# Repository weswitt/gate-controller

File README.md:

This project is a PCB design for controlling a Liftmaster gate operator from Home Assistant. 

The PCB design was done in KiCad 8.0, which is an open source electronic design tool. This project includes all of the KiCad project files so that you can modify the PCB if needed. I've also included a GERBER.ZIP file that can be used to simply have the PCB printed by someplace like JLPCB.

This project includes a bill of materials with URLs for all the parts necessary to build the board. I've sourced the part from DigiKey and Amazon.

The integration of the gate controller into Home Assistant is accomplished using ESPHome. This project includes the YAML file necessary to build and flash the firmware into the gate controller. You'll need to edit the YAML file and change the lines specified to customize to your environment.

This project includes datasheets for every component used on the gate controller board.

The gate controller board uses an ESP32-WROOM-32U microcontroller. This variant of the ESP32 uses an external antenna to improve the Wifi connectivity.

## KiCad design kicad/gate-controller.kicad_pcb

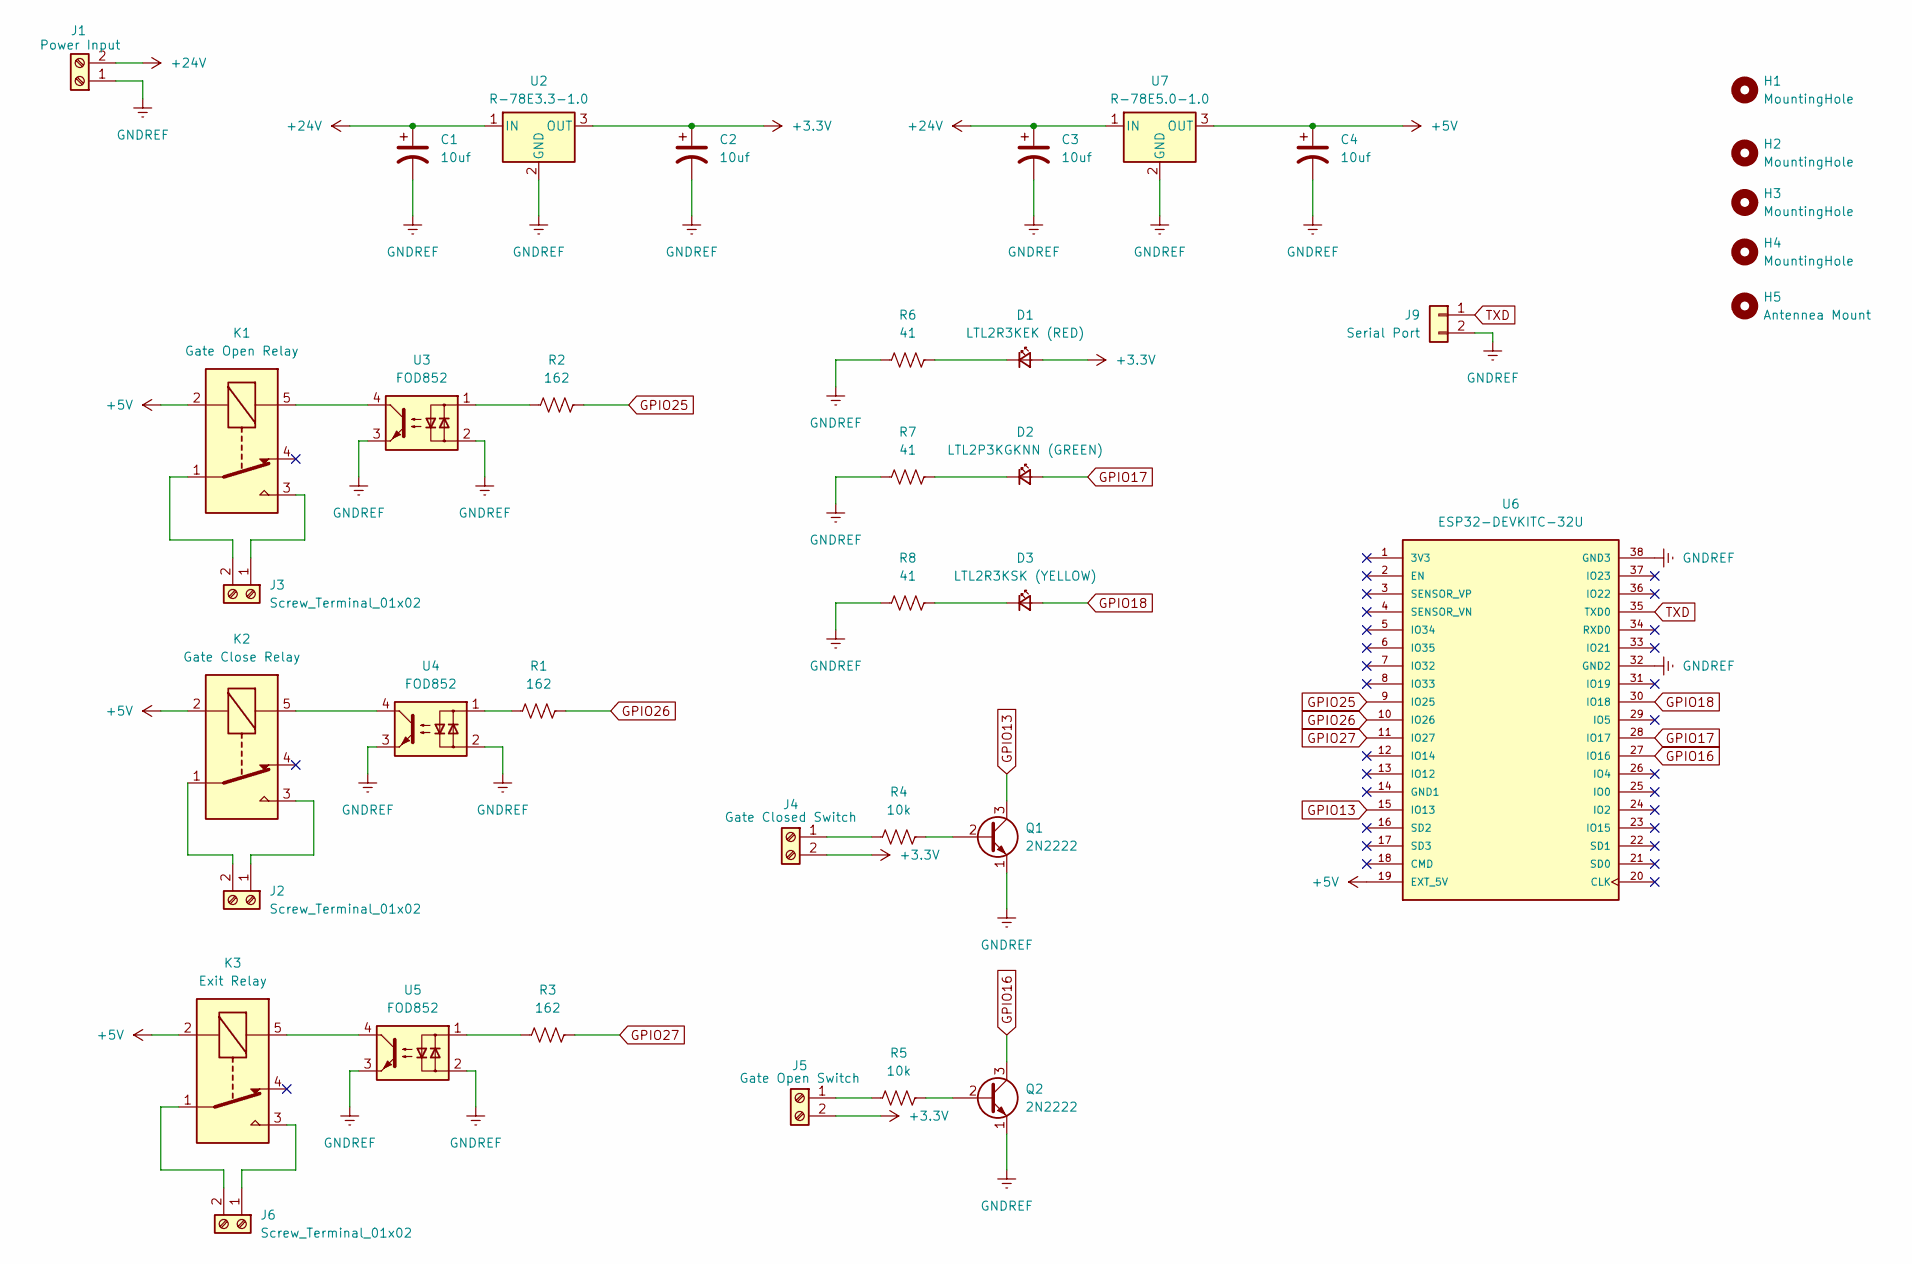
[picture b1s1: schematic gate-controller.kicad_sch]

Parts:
C1, C2, C3, C4: 10uf; C_Radial_D5.0mm_H11.0mm_P2.00mm
D1: LTL2R3KEK (RED); LED_D5.0mm_Clear
D2: LTL2P3KGKNN (GREEN); LED_D5.0mm_Clear
D3: LTL2R3KSK (YELLOW); LED_D5.0mm_Clear
H1, H2, H3, H4: MountingHole; MountingHole_5.3mm_M5
H5: Antennea Mount; MountingHole_6.5mm
J1: Power Input; TerminalBlock_Phoenix_PT-1,5-2-5.0-H_1x02_P5.00mm_Horizontal
J2, J3, J6: Screw_Terminal_01x02; TerminalBlock_Phoenix_PT-1,5-2-5.0-H_1x02_P5.00mm_Horizontal
J4: Gate Closed Switch; TerminalBlock_Phoenix_PT-1,5-2-5.0-H_1x02_P5.00mm_Horizontal
J5: Gate Open Switch; TerminalBlock_Phoenix_PT-1,5-2-5.0-H_1x02_P5.00mm_Horizontal
J9: Serial Port; PinHeader_1x02_P2.54mm_Vertical
K1: Gate Open Relay; Relay_SPDT_Omron-G5LE-1
K2: Gate Close Relay; Relay_SPDT_Omron-G5LE-1
K3: Exit Relay; Relay_SPDT_Omron-G5LE-1
Q1, Q2: 2N2222; TO-92_Reverse
R1, R2, R3: 162; R_Axial_DIN0207_L6.3mm_D2.5mm_P7.62mm_Horizontal
R4, R5: 10k; R_Axial_DIN0207_L6.3mm_D2.5mm_P7.62mm_Horizontal
R6, R7, R8: 41; R_Axial_DIN0207_L6.3mm_D2.5mm_P7.62mm_Horizontal
U2: R-78E3.3-1.0; Converter_DCDC_RECOM_R-78E-0.5_THT
U3, U4, U5: FOD852; DIP-4_W7.62mm
U6: ESP32-DEVKITC-32U
U7: R-78E5.0-1.0; Converter_DCDC_RECOM_R-78E-0.5_THT

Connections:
+3.3V: C2.1, D1.2 (A), J4.2, J5.2, U2.3 (OUT)
+5V: C4.1, K1.2, K2.2, K3.2, U6.19 (EXT_5V), U7.3 (OUT)
+24V: C1.1, C3.1, J1.2, U2.1 (IN), U7.1 (IN)
GNDREF: C1.2, C2.2, C3.2, C4.2, J1.1, J9.2, Q1.1 (E), Q2.1 (E), R6.1, R7.1, R8.1, U2.2 (GND), U3.2, U3.3, U4.2, U4.3, U5.2, U5.3, U6.32 (GND2), U6.38 (GND3), U7.2 (GND)
GPIO13: Q1.3 (C), U6.15 (IO13)
GPIO16: Q2.3 (C), U6.27 (IO16)
GPIO17: D2.2 (A), U6.28 (IO17)
GPIO18: D3.2 (A), U6.30 (IO18)
GPIO25: R2.2, U6.9 (IO25)
GPIO26: R1.2, U6.10 (IO26)
GPIO27: R3.2, U6.11 (IO27)
unnamed: D1.1 (K), R6.2
unnamed: D2.1 (K), R7.2
unnamed: D3.1 (K), R8.2
unnamed: J2.1, K2.3
unnamed: J2.2, K2.1
unnamed: J3.1, K1.3
unnamed: J3.2, K1.1
unnamed: J4.1, R4.1
unnamed: J5.1, R5.1
unnamed: J6.1, K3.3
unnamed: J6.2, K3.1
unnamed: K1.5, U3.4
unnamed: K2.5, U4.4
unnamed: K3.5, U5.4
unnamed: Q1.2 (B), R4.2
unnamed: Q2.2 (B), R5.2
unnamed: R1.1, U4.1
unnamed: R2.1, U3.1
unnamed: R3.1, U5.1
TXD: J9.1, U6.35 (TXD0)

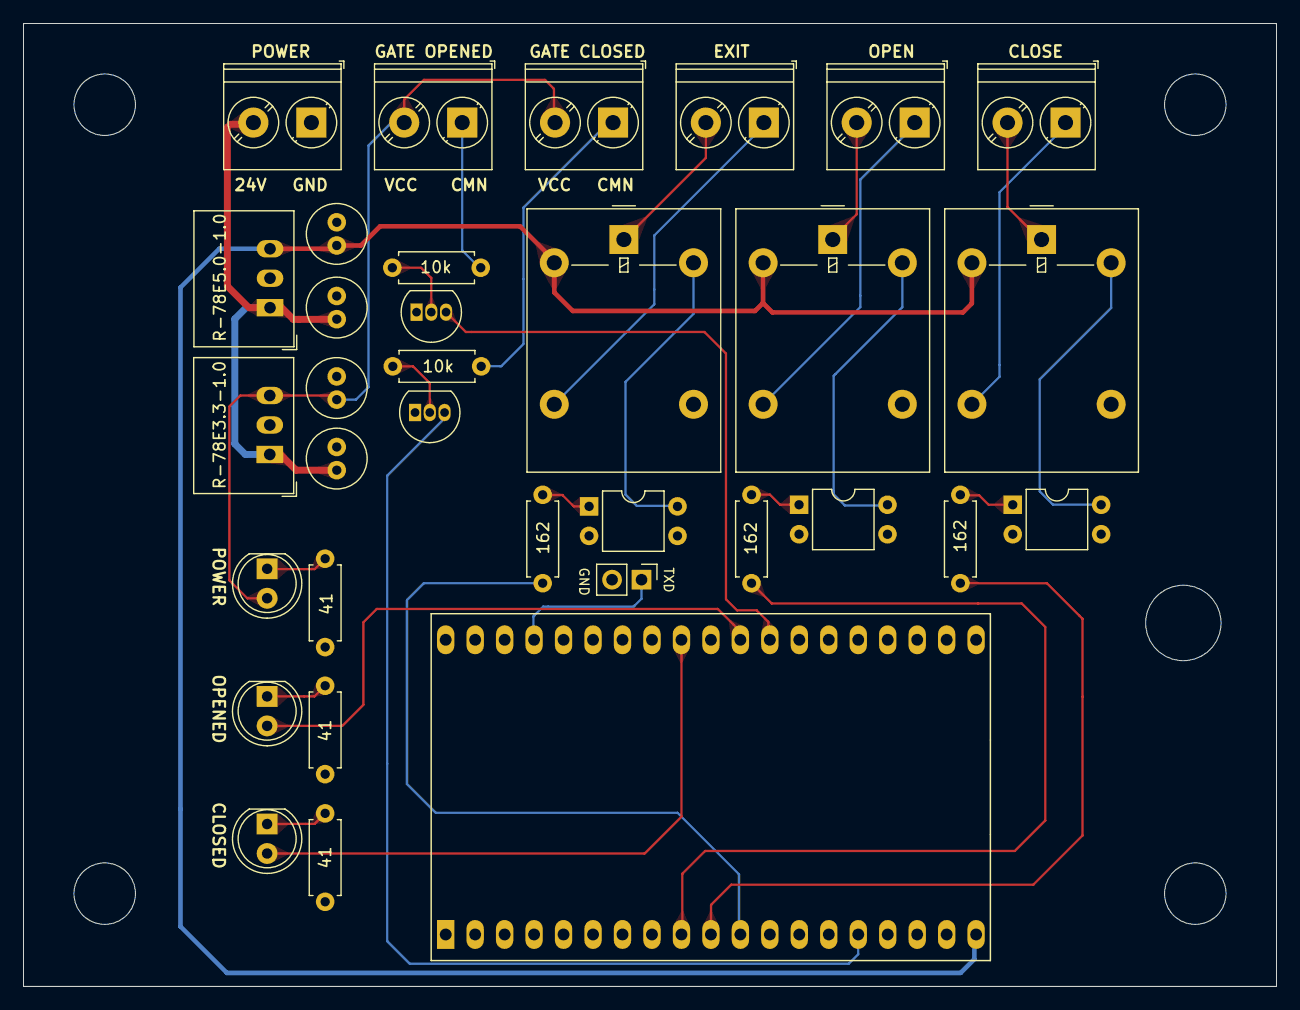
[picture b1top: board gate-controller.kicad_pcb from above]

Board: 2 copper layers, 108.0 x 83.0 mm, 38 parts (0 on the bottom side), 31 nets.

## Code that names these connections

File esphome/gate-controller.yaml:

esp32:
  board: esp32doit-devkit-v1

esphome:
  name: **your-name**
  friendly_name: **your-friendly-name**

api:

logger:
  baud_rate: 0
#  baud_rate: 115200
#  level: VERBOSE

ota:

web_server:
  port: 80

wifi:
  ssid: **your-ssid**
  password: **your-password**
  manual_ip:
    static_ip: **your-ip**
    gateway: **your-gateway**
    subnet: **your-subnet**

button:
  - platform: restart
    name: Restart

text_sensor:
  - platform: wifi_info
    ip_address:
      name: "IP Address"
      id: ip_address
      icon: mdi:ip-network
    ssid:
      name: SSID
      id: ssid
      icon: mdi:wifi

sensor:
  - platform: uptime
    name: Uptime
  - platform: wifi_signal
    name: "WiFi Signal"
    id: wifi_signal_strength
    update_interval: 60s
    icon: mdi:wifi-strength-1

light:
  - platform: status_led
    id: opened_led
    pin: GPIO17
    restore_mode: ALWAYS_OFF
  - platform: status_led
    id: closed_led
    pin: GPIO18
    restore_mode: ALWAYS_OFF

binary_sensor:
  - platform: gpio
    filters:
      - invert:
    pin:
      number: GPIO13
      mode:
        input: true
        pullup: true
    name: "Closed Sensor"
    id: closed_sensor
    icon: mdi:gate
    on_press:
      then:
        - light.turn_on: closed_led
        - light.turn_off: opened_led
  - platform: gpio
    filters:
      - invert:
    pin:
      number: GPIO16
      mode:
        input: true
        pullup: true
    name: "Open Sensor"
    id: open_sensor
    icon: mdi:gate-open
    on_press:
      then:
        - light.turn_on: opened_led
        - light.turn_off: closed_led

switch:
  - platform: gpio
    pin: GPIO25
    name: "Open Switch"
    id: open_switch
    icon: mdi:gate
    on_turn_on:
      - delay: 200ms
      - switch.turn_off: open_switch
  - platform: gpio
    pin: GPIO26
    name: "Close Switch"
    id: close_switch
    icon: mdi:gate
    on_turn_on:
      - delay: 200ms
      - switch.turn_off: close_switch
  - platform: gpio
    pin: GPIO27
    name: "Exit Switch"
    id: exit_switch
    icon: mdi:gate
    on_turn_on:
      - delay: 200ms
      - switch.turn_off: exit_switch

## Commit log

2024-08-17 Initial files added
2024-08-17 Initial files
